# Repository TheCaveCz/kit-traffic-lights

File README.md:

# Traffic Lights / Semafory

You can find English version [here](README(EN).md).
Stavebnice přechodu pro chodce řízeného semafory. Tlačítko BTN1 dává signál pro chodce, tlačítko BTN3 vypne křižovatku.

* [Návod na stavbu](doc/manual-cz.md) ([PDF](doc/manual-cz.pdf))
* [Nahrání nového firmware](doc/firmware-cz.md)

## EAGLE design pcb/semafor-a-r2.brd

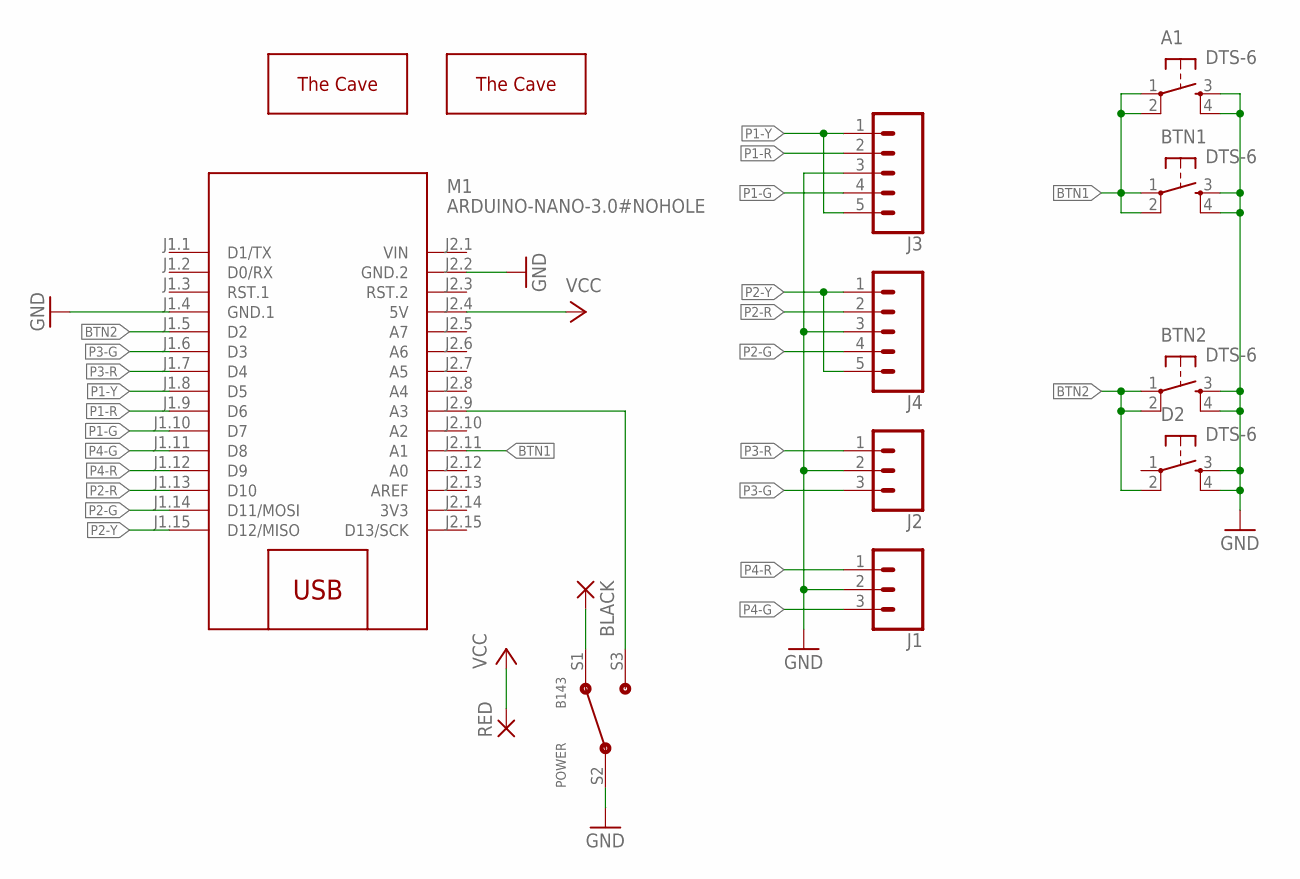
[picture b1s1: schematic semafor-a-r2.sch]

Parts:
A1: DTS-6
BLACK: WIREPAD2,54/1,0; 2,54/1,0
BTN1, BTN2: DTS-6
D2: DTS-6
J1, J2: CONN_031X03_NO_SILK; 1X03_NO_SILK
J3, J4: CONN_05NO_SILK; 1X05_NO_SILK
M1: ARDUINO-NANO-3.0#NOHOLE; ARDUINO-NANO-3.0
POWER: B143
RED: WIREPAD2,54/1,0; 2,54/1,0
U$1: THECAVE_LOGO_NEW_TOP_SMALL; NEW_LOGO_SMALL_TOP
U$2: THECAVE_LOGO_NEW_BOTTOM; NEW_LOGO_BOTTOM

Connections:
3V3: M1.J2.14 (3V3)
BTN1: A1.1, A1.2, BTN1.1, BTN1.2, M1.J2.11 (A1)
BTN2: BTN2.1, BTN2.2, D2.2, M1.J1.5 (D2)
GND: A1.3, A1.4, BTN1.3, BTN1.4, BTN2.3, BTN2.4, D2.3, D2.4, J1.2, J2.2, J3.3, J4.3, M1.J1.4 (GND.1), M1.J2.2 (GND.2), POWER.S2 (COM)
unnamed: M1.J2.9 (A3), POWER.S3 (S2)
unnamed: BLACK.1, POWER.S1
P1-G: J3.4, M1.J1.10 (D7)
P1-R: J3.2, M1.J1.9 (D6)
P1-Y: J3.1, J3.5, M1.J1.8 (D5)
P2-G: J4.4, M1.J1.14 (D11/MOSI)
P2-R: J4.2, M1.J1.13 (D10)
P2-Y: J4.1, J4.5, M1.J1.15 (D12/MISO)
P3-G: J2.3, M1.J1.6 (D3)
P3-R: J2.1, M1.J1.7 (D4)
P4-G: J1.3, M1.J1.11 (D8)
P4-R: J1.1, M1.J1.12 (D9)
VCC: M1.J2.4 (5V), RED.1
VIN: M1.J2.1 (VIN)

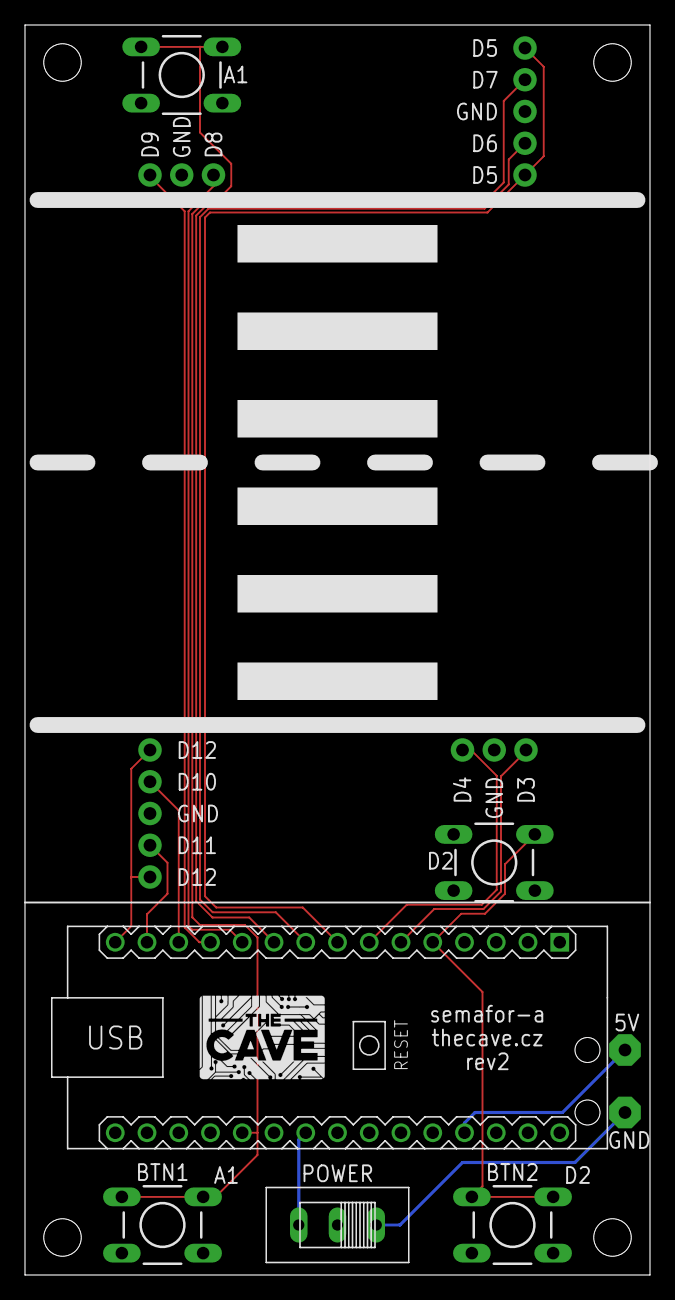
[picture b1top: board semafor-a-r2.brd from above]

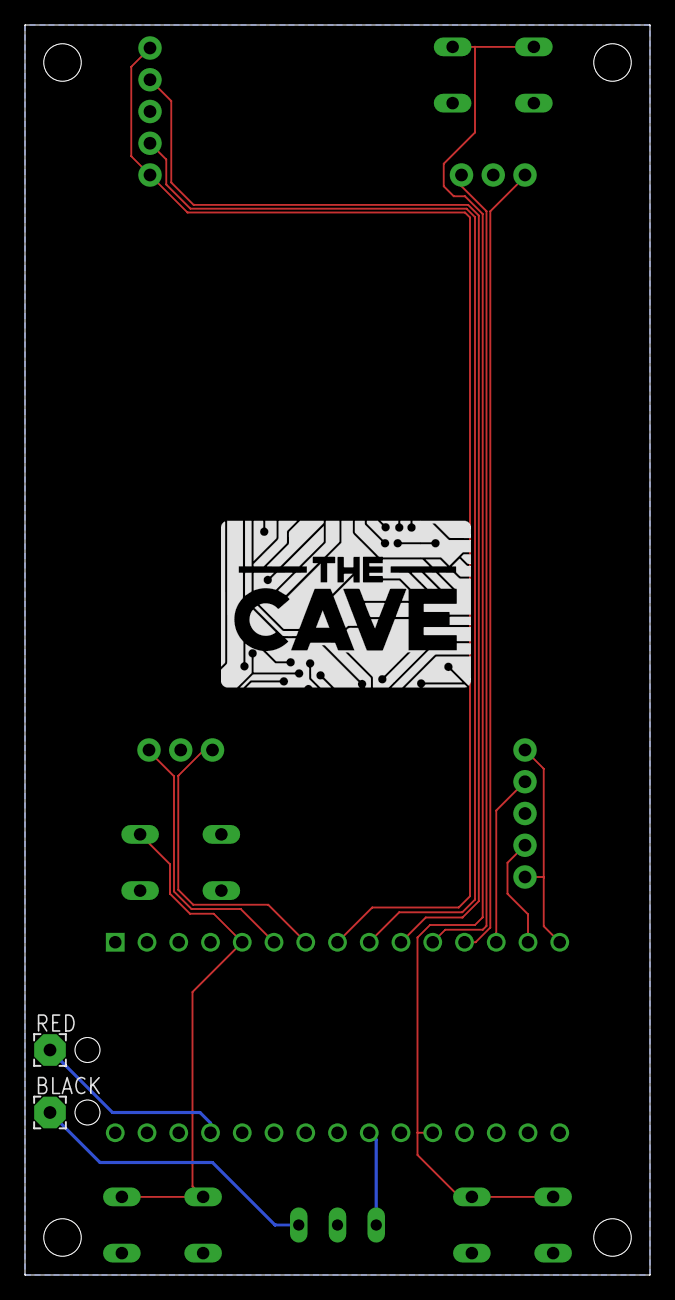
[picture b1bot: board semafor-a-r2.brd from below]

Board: 2 copper layers, 50.0 x 100.0 mm, 14 parts (2 on the bottom side), 16 nets.

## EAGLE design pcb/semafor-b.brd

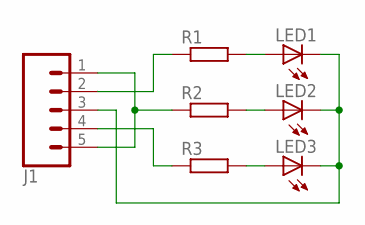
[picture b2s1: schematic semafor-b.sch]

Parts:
J1: CONN_05NO_SILK; 1X05_NO_SILK
LED1, LED2, LED3: LED5MM
R1, R2, R3: R-EU_0207/7; 0207/7

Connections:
unnamed: LED3.A, R3.2
unnamed: LED2.A, R2.2
unnamed: LED1.A, R1.2
unnamed: J1.3, LED1.K (C), LED2.K (C), LED3.K (C)
unnamed: J1.2, R1.1
unnamed: J1.4, R3.1
unnamed: J1.1, J1.5, R2.1

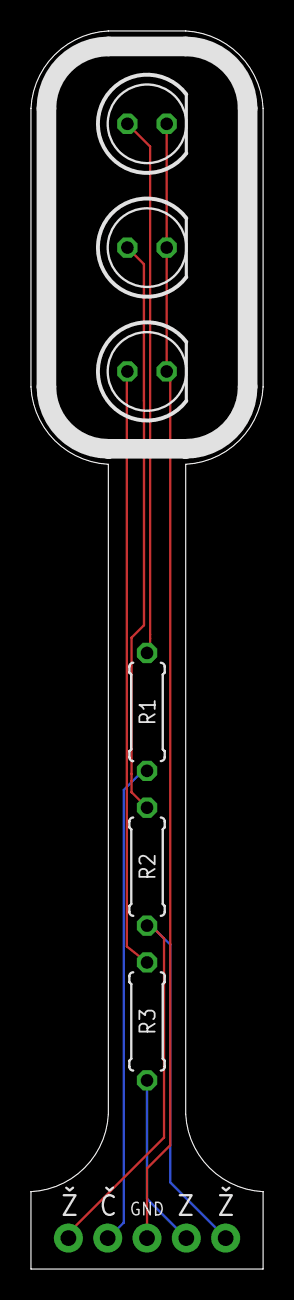
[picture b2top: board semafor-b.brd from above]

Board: 2 copper layers, 15.0 x 80.0 mm, 7 parts (0 on the bottom side), 7 nets.

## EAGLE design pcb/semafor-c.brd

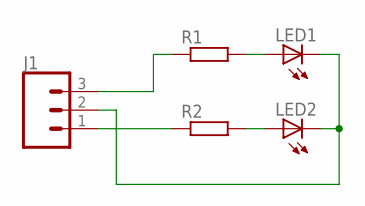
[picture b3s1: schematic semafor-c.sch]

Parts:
J1: CONN_031X03_NO_SILK; 1X03_NO_SILK
LED1, LED2: LED5MM
R1, R2: R-EU_0207/7; 0207/7

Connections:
unnamed: LED2.A, R2.2
unnamed: LED1.A, R1.2
unnamed: J1.2, LED1.K (C), LED2.K (C)
unnamed: J1.3, R1.1
unnamed: J1.1, R2.1

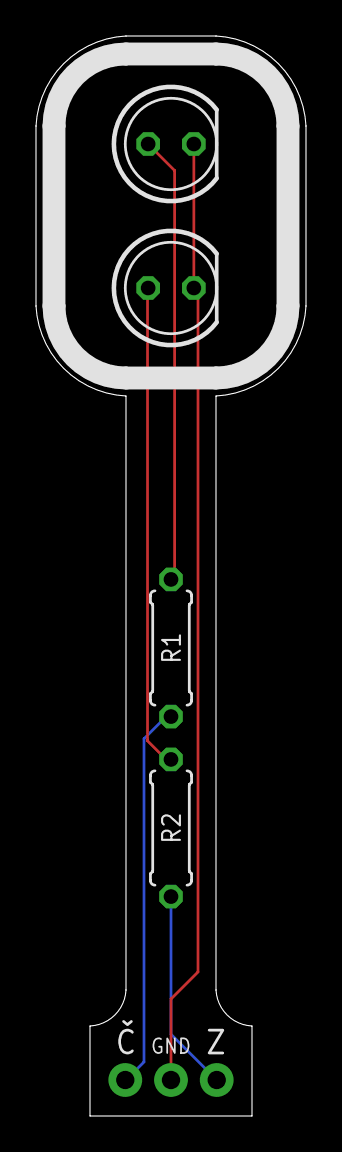
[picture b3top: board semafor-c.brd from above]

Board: 2 copper layers, 15.0 x 60.0 mm, 5 parts (0 on the bottom side), 5 nets.

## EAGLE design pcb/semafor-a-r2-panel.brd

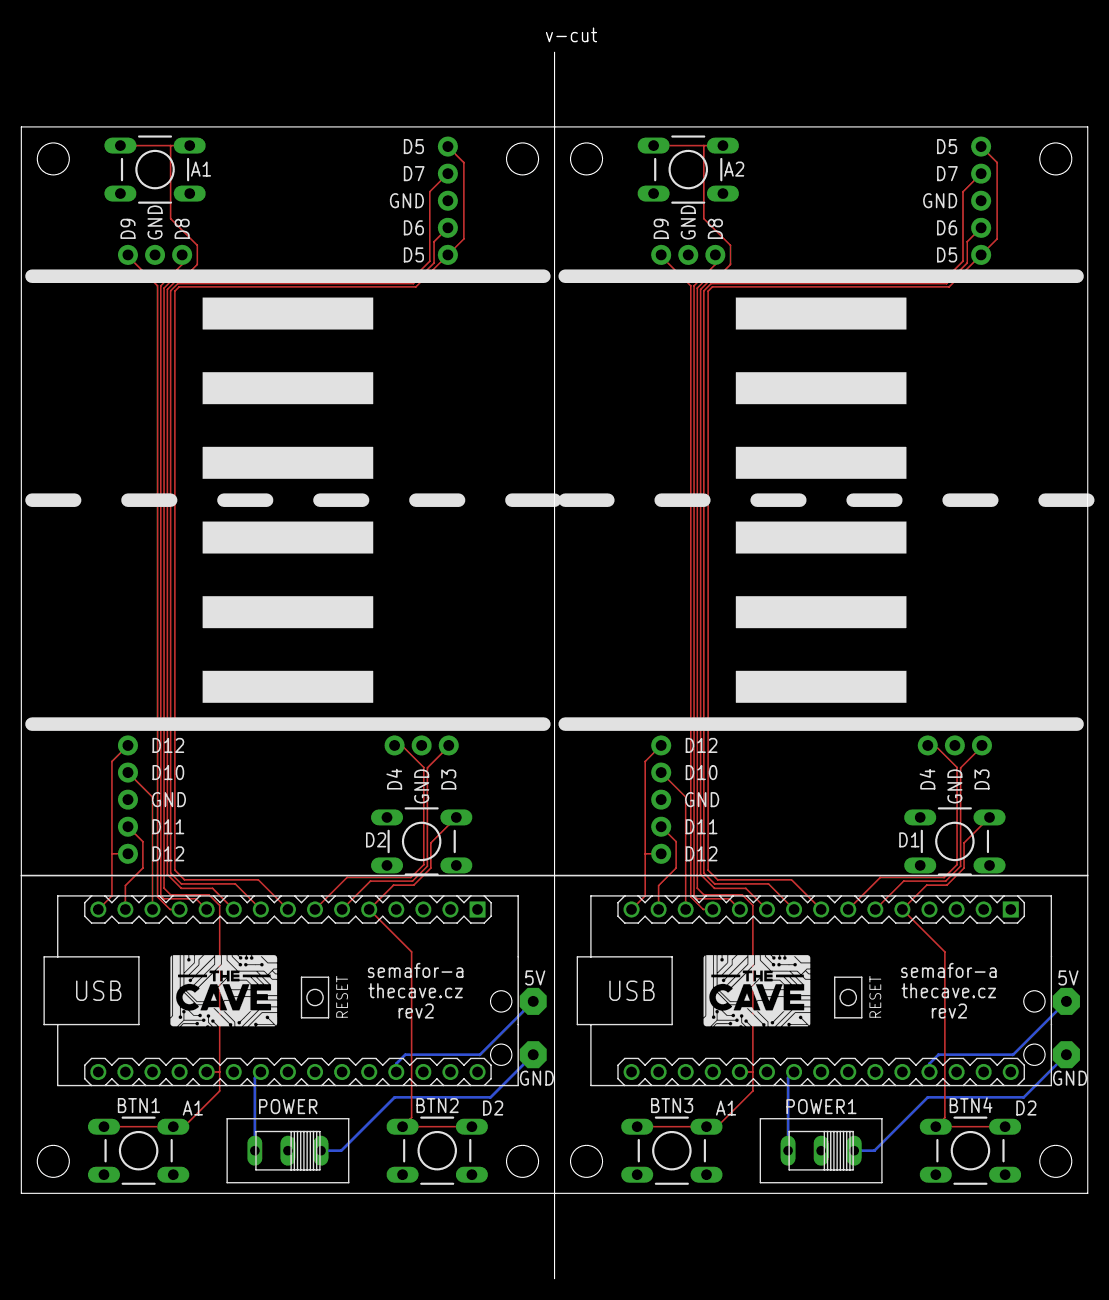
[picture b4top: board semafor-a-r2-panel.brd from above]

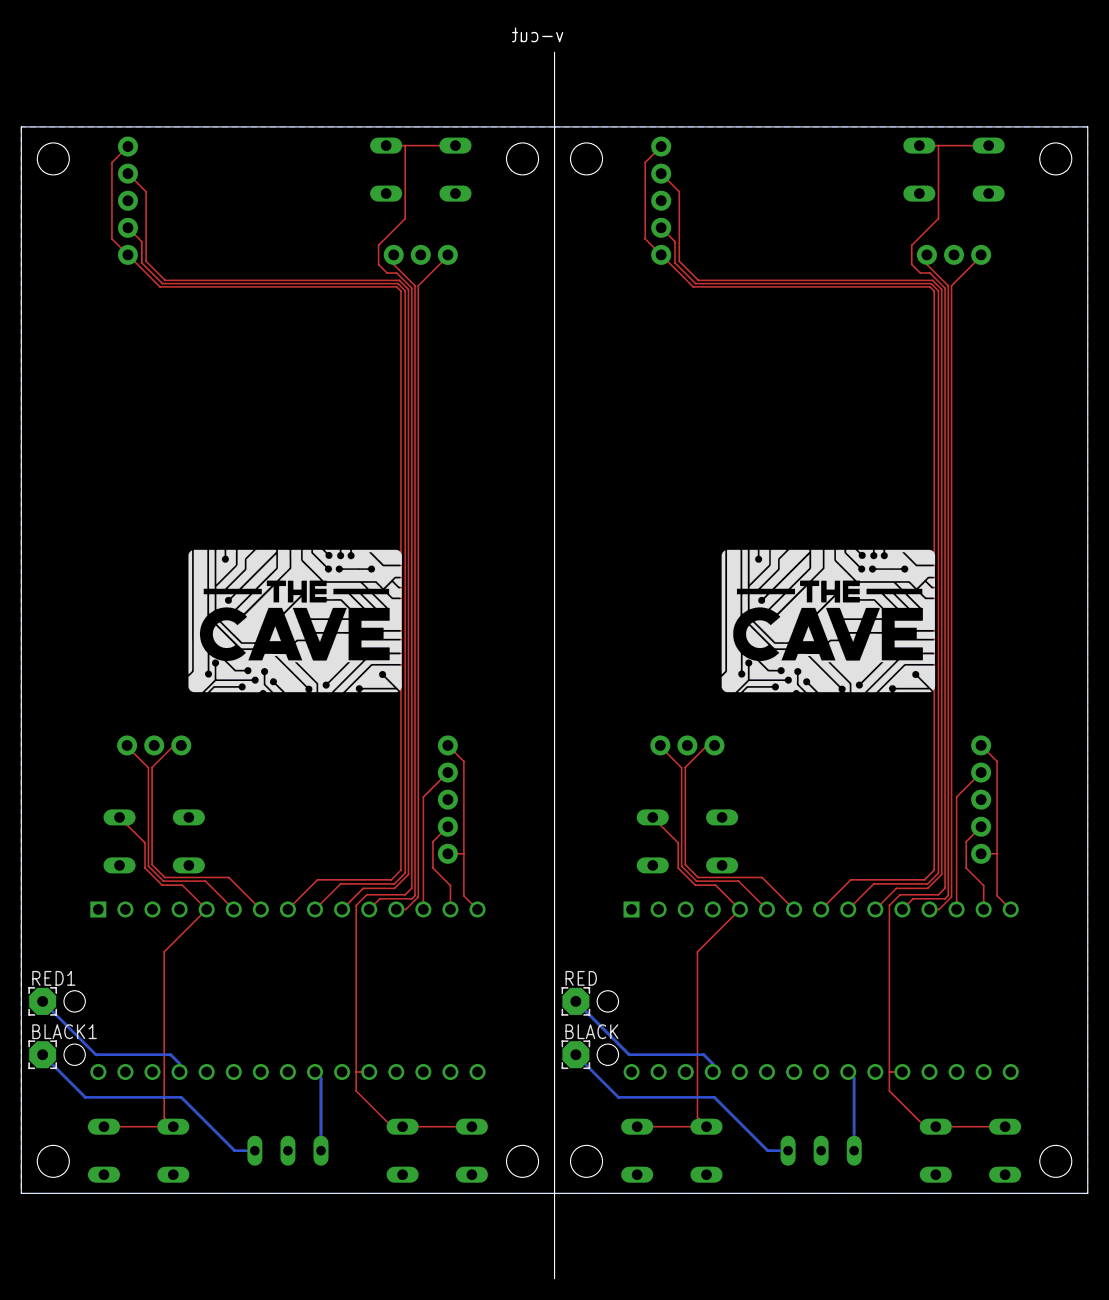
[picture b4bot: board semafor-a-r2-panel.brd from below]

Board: 2 copper layers, 100.0 x 117.9 mm, 28 parts (4 on the bottom side), 32 nets.

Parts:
A1, A2: DTS-6
BLACK, BLACK1: 2,54/1,0
BTN1, BTN2, BTN3, BTN4: DTS-6
D1, D2: DTS-6
J1, J2, J5, J6: 1X03_NO_SILK
J3, J4, J7, J8: 1X05_NO_SILK
M1, M2: ARDUINO-NANO-3.0#NOHOLE; ARDUINO-NANO-3.0
POWER, POWER1: B143
RED, RED1: 2,54/1,0
U$1, U$3: THECAVE_LOGO_NEW_TOP_SMALL; NEW_LOGO_SMALL_TOP
U$2, U$4: THECAVE_LOGO_NEW_BOTTOM; NEW_LOGO_BOTTOM

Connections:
BTN1: A1.1, A1.2, BTN1.1, BTN1.2, M1.J2.11
BTN2: BTN2.1, BTN2.2, D2.2, M1.J1.5
BTN3: A2.1, A2.2, BTN3.1, BTN3.2, M2.J2.11
BTN4: BTN4.1, BTN4.2, D1.2, M2.J1.5
GND: A1.3, A1.4, BTN1.3, BTN1.4, BTN2.3, BTN2.4, D2.3, D2.4, J1.2, J2.2, J3.3, J4.3, M1.J1.4, M1.J2.2, POWER.S2
GND1: A2.3, A2.4, BTN3.3, BTN3.4, BTN4.3, BTN4.4, D1.3, D1.4, J5.2, J6.2, J7.3, J8.3, M2.J1.4, M2.J2.2, POWER1.S2
unnamed: M1.J2.9, POWER.S3
unnamed: BLACK.1, POWER.S1
unnamed: M2.J2.9, POWER1.S3
unnamed: BLACK1.1, POWER1.S1
P1-G: J3.4, M1.J1.10
P1-G1: J7.4, M2.J1.10
P1-R: J3.2, M1.J1.9
P1-R1: J7.2, M2.J1.9
P1-Y: J3.1, J3.5, M1.J1.8
P1-Y1: J7.1, J7.5, M2.J1.8
P2-G: J4.4, M1.J1.14
P2-G1: J8.4, M2.J1.14
P2-R: J4.2, M1.J1.13
P2-R1: J8.2, M2.J1.13
P2-Y: J4.1, J4.5, M1.J1.15
P2-Y1: J8.1, J8.5, M2.J1.15
P3-G: J2.3, M1.J1.6
P3-G1: J6.3, M2.J1.6
P3-R: J2.1, M1.J1.7
P3-R1: J6.1, M2.J1.7
P4-G: J1.3, M1.J1.11
P4-G1: J5.3, M2.J1.11
P4-R: J1.1, M1.J1.12
P4-R1: J5.1, M2.J1.12
VCC: M1.J2.4, RED.1
VCC1: M2.J2.4, RED1.1

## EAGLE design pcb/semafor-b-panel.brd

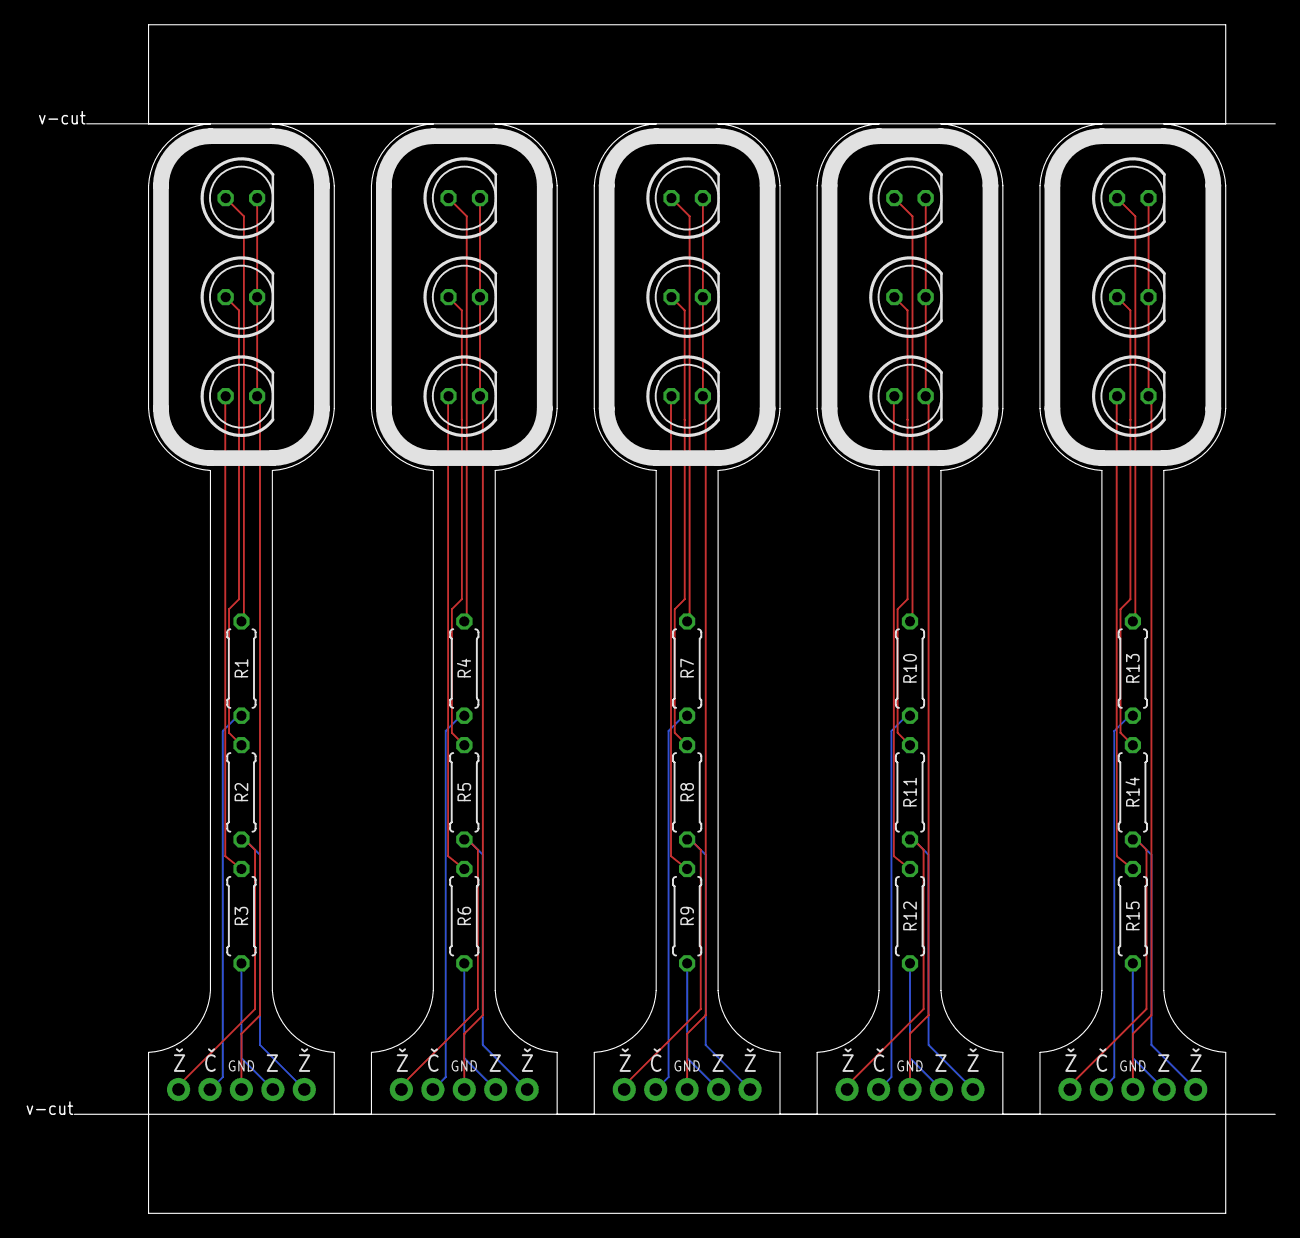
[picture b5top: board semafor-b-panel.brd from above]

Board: 2 copper layers, 101.0 x 96.0 mm, 35 parts (0 on the bottom side), 35 nets.

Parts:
J1, J2, J3, J4, J5: 1X05_NO_SILK
LED1, LED2, LED3, LED4, LED5, LED6, LED7, LED8, LED9, LED10, LED11, LED12, LED13, LED14, LED15: LED5MM
R1, R2, R3, R4, R5, R6, R7, R8, R9, R10, R11, R12, R13, R14, R15: 0207/7

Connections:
unnamed: LED3.A, R3.2
unnamed: LED2.A, R2.2
unnamed: LED1.A, R1.2
unnamed: J1.3, LED1.K, LED2.K, LED3.K
unnamed: J1.2, R1.1
unnamed: J1.4, R3.1
unnamed: J1.1, J1.5, R2.1
unnamed: J2.3, LED4.K, LED5.K, LED6.K
unnamed: J2.2, R4.1
unnamed: J2.4, R6.1
unnamed: J2.1, J2.5, R5.1
unnamed: LED6.A, R6.2
unnamed: LED5.A, R5.2
unnamed: LED4.A, R4.2
unnamed: J3.3, LED7.K, LED8.K, LED9.K
unnamed: J3.2, R7.1
unnamed: J3.4, R9.1
unnamed: J3.1, J3.5, R8.1
unnamed: LED9.A, R9.2
unnamed: LED8.A, R8.2
unnamed: LED7.A, R7.2
unnamed: J4.3, LED10.K, LED11.K, LED12.K
unnamed: J4.2, R10.1
unnamed: J4.4, R12.1
unnamed: J4.1, J4.5, R11.1
unnamed: LED12.A, R12.2
unnamed: LED11.A, R11.2
unnamed: LED10.A, R10.2
unnamed: J5.3, LED13.K, LED14.K, LED15.K
unnamed: J5.2, R13.1
unnamed: J5.4, R15.1
unnamed: J5.1, J5.5, R14.1
unnamed: LED15.A, R15.2
unnamed: LED14.A, R14.2
unnamed: LED13.A, R13.2

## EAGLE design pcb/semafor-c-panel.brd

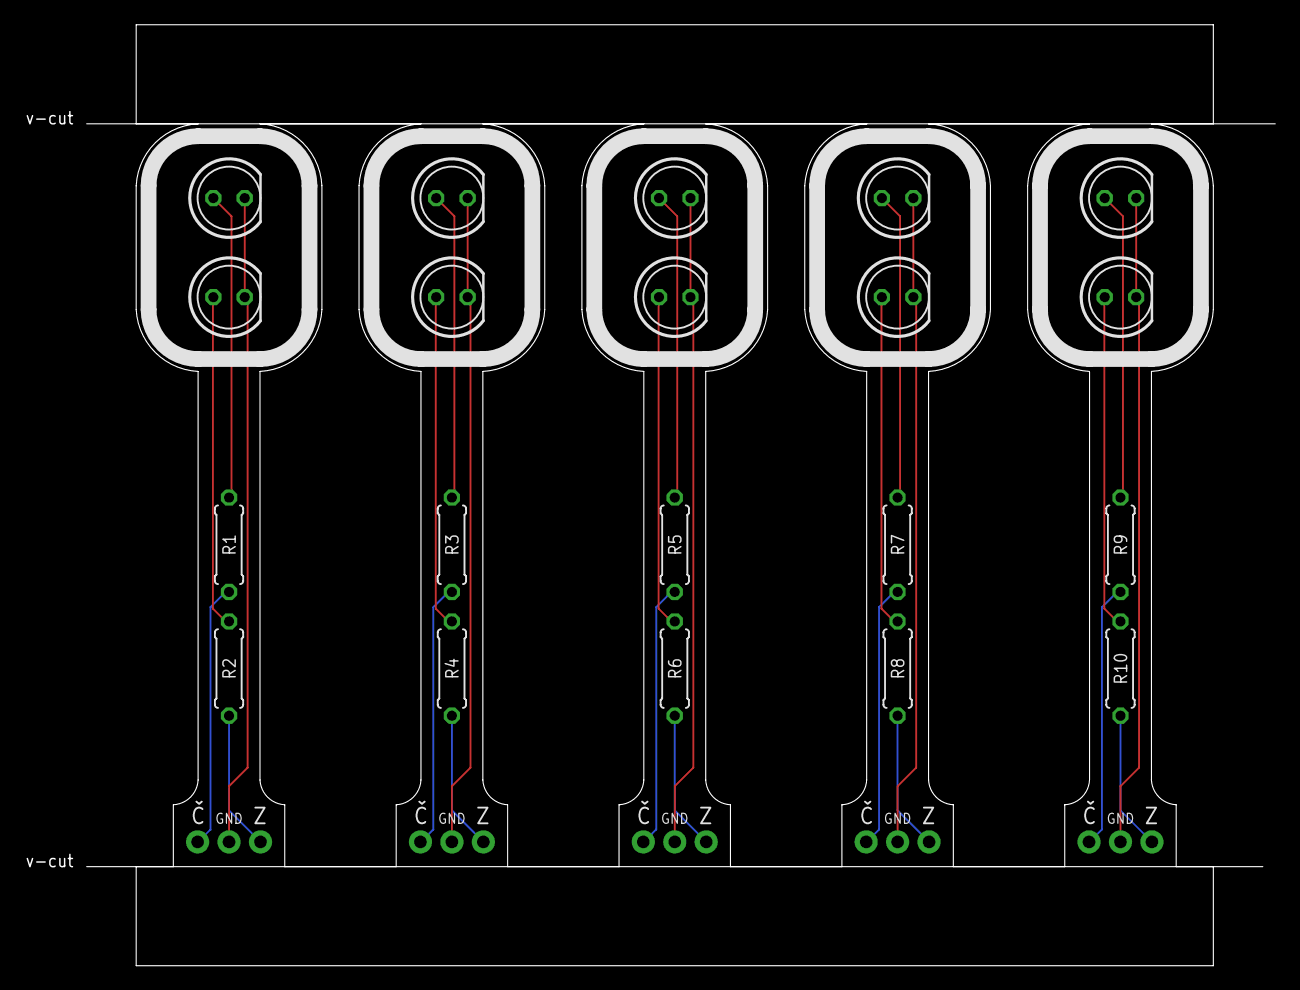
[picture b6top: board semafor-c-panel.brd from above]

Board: 2 copper layers, 101.0 x 76.0 mm, 25 parts (0 on the bottom side), 25 nets.

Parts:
J1, J2, J3, J4, J5: 1X03_NO_SILK
LED1, LED2, LED3, LED4, LED5, LED6, LED7, LED8, LED9, LED10: LED5MM
R1, R2, R3, R4, R5, R6, R7, R8, R9, R10: 0207/7

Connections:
unnamed: LED2.A, R2.2
unnamed: J2.2, LED3.K, LED4.K
unnamed: LED1.A, R1.2
unnamed: J1.2, LED1.K, LED2.K
unnamed: J1.3, R1.1
unnamed: J1.1, R2.1
unnamed: J2.3, R3.1
unnamed: J2.1, R4.1
unnamed: LED4.A, R4.2
unnamed: LED3.A, R3.2
unnamed: J3.2, LED5.K, LED6.K
unnamed: J3.3, R5.1
unnamed: J3.1, R6.1
unnamed: LED6.A, R6.2
unnamed: LED5.A, R5.2
unnamed: J4.2, LED7.K, LED8.K
unnamed: J4.3, R7.1
unnamed: J4.1, R8.1
unnamed: LED8.A, R8.2
unnamed: LED7.A, R7.2
unnamed: J5.2, LED9.K, LED10.K
unnamed: J5.3, R9.1
unnamed: J5.1, R10.1
unnamed: LED10.A, R10.2
unnamed: LED9.A, R9.2

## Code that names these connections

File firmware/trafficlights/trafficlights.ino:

/*
   Traffic Lights kit firmware

   The Cave, 2019
   https://thecave.cz

   Licensed under MIT License (see LICENSE file for details)

   Board: Arduino Nano
   Processor: ATmega328p

   Using TaskScheduler and OneButton libraries

*/
#include <OneButton.h>
#include <TaskScheduler.h>

#define PIN_BTN1 A1
#define PIN_BTN2 A2
#define PIN_BTN3 2

#define PIN_CAR_RED1 10
#define PIN_CAR_YELLOW1 12
#define PIN_CAR_GREEN1 11

#define PIN_CAR_RED2 6
#define PIN_CAR_YELLOW2 5
#define PIN_CAR_GREEN2 7

#define PIN_WALK_RED1 3
#define PIN_WALK_GREEN1 4

#define PIN_WALK_RED2 9
#define PIN_WALK_GREEN2 8


#define SIG_CAR_RED 0b00100
#define SIG_CAR_YELLOW 0b00010
#define SIG_CAR_GREEN 0b00001
#define SIG_WALK_RED 0b10000
#define SIG_WALK_GREEN 0b01000

#define SIG_SPEEDUP 0b00100000
#define SIG_TURNOFF 0b01000000
#define SIG_WALK    0b10000000


void keep_me_here() {}

Scheduler scheduler;
Task signalTask(1000, TASK_FOREVER, &signalWorkCb, &scheduler,  true);
uint8_t signalPos;
uint8_t signalRepeats;
uint8_t signalCurrent;
bool signalTurnOffFlag;
OneButton buttonWalk(PIN_BTN1, true);
OneButton buttonTurnOff(PIN_BTN3, true);


const uint8_t signalProgram[] PROGMEM = {
  SIG_WALK_RED | SIG_CAR_YELLOW | SIG_TURNOFF, 2,
  SIG_WALK_RED | SIG_CAR_RED, 2,
  SIG_WALK_GREEN | SIG_CAR_RED | SIG_SPEEDUP, 5 ,
  SIG_WALK_RED | SIG_CAR_RED, 2,
  SIG_WALK_RED | SIG_CAR_RED | SIG_CAR_YELLOW | SIG_TURNOFF, 2,
  SIG_WALK_RED | SIG_CAR_GREEN | SIG_SPEEDUP | SIG_WALK, 20,

  0, 0
};


void signalSet(const uint8_t s) {
  digitalWrite(PIN_WALK_RED1, s & SIG_WALK_RED);
  digitalWrite(PIN_WALK_RED2, s & SIG_WALK_RED);

  digitalWrite(PIN_WALK_GREEN1, s & SIG_WALK_GREEN);
  digitalWrite(PIN_WALK_GREEN2, s & SIG_WALK_GREEN);

  digitalWrite(PIN_CAR_RED1, s & SIG_CAR_RED);
  digitalWrite(PIN_CAR_RED2, s & SIG_CAR_RED);

  digitalWrite(PIN_CAR_YELLOW1, s & SIG_CAR_YELLOW);
  digitalWrite(PIN_CAR_YELLOW2, s & SIG_CAR_YELLOW);

  digitalWrite(PIN_CAR_GREEN1, s & SIG_CAR_GREEN);
  digitalWrite(PIN_CAR_GREEN2, s & SIG_CAR_GREEN);
}

void signalAdvance() {
  if (signalTurnOffFlag && (signalCurrent & SIG_TURNOFF)) {
    signalTurnOffFlag = false;
    signalCurrent = 0;
    signalTask.setCallback(signalBlinkCb);
    signalTask.enable();
    return;
  }
  signalPos++;

  signalCurrent = pgm_read_byte(signalProgram + signalPos * 2);
  signalRepeats = pgm_read_byte(signalProgram + signalPos * 2 + 1);

  signalSet(signalCurrent);
  if (signalRepeats == 0) {
    signalPos = 0xff;
    signalAdvance();
  }
}

void signalWorkCb() {
  if (signalRepeats == 0) {
    signalAdvance();
  }
  signalRepeats--;
}

void signalBlinkCb() {
  signalSet(signalTask.getRunCounter() & 1 ? 0 : SIG_CAR_YELLOW);
  if (signalTurnOffFlag) {
    signalTurnOffFlag = false;
    signalRepeats = 0;
    signalPos = 0xff;
    signalTask.setCallback(signalWorkCb);
    signalTask.enable();
  }
}

void buttonWalkClick() {
  if (signalCurrent & SIG_WALK) {
    signalAdvance();
  }
}

void buttonTurnOffClick() {
  signalTurnOffFlag = true;
  if (signalCurrent & SIG_SPEEDUP) {
    signalAdvance();
  }
}

void setup() {
  signalPos = 0;

  pinMode(PIN_WALK_RED1, OUTPUT);
  pinMode(PIN_WALK_RED2, OUTPUT);
  pinMode(PIN_WALK_GREEN1, OUTPUT);
  pinMode(PIN_WALK_GREEN2, OUTPUT);
  pinMode(PIN_CAR_RED1, OUTPUT);
  pinMode(PIN_CAR_RED2, OUTPUT);
  pinMode(PIN_CAR_YELLOW1, OUTPUT);
  pinMode(PIN_CAR_YELLOW2, OUTPUT);
  pinMode(PIN_CAR_GREEN1, OUTPUT);
  pinMode(PIN_CAR_GREEN2, OUTPUT);

  buttonWalk.attachClick(buttonWalkClick);
  buttonTurnOff.attachClick(buttonTurnOffClick);

  signalPos = 0xff;
  signalAdvance();
}

void loop() {
  buttonWalk.tick();
  buttonTurnOff.tick();
  scheduler.execute();
}

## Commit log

2019-05-14 Add pcbs
2019-06-20 Add manual
2019-06-20 Add missing ground wire to PCB and update gerbers
2019-06-20 Add firmware
2019-06-20 Add firmware instructions
2019-06-20 Fix typo
2019-06-23 Changed to english version
2019-06-23 added link to english readme
2019-06-23 Corrected the link
2019-11-28 Add power switch and external voltage supply pins
2019-12-05 Add panel for semafor-a-r2

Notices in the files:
parts and their libraries:
SparkFun-Connectors: Licensing: Creative Commons ShareAlike 4.0 International - https://creativecommons.org/licenses/by-sa/4.0
